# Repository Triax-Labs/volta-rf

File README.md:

> [!CAUTION]
> We claim **ZERO responsibility** against individuals who choose to operate, produce or sell this hardware. This repository exists strictly for educational & research purposes only.
>
> All tests for this hardware were done inside a controlled lab environment with all the proper local licenses needed for needed experiments.
>
> Please mind your local radio & telecommunication laws.

# VoltaRF

VoltaRF is a homebrew software defined radio (SDR), it is based on parts found inside a cheap 'n old satellite DVB-S television receiver.

VoltaRF could also be used as an expressive development board around the CH32H417 flagship platform, all GPIOs are exposed!

## Background

Due to the fact that RTL-SDRs are quite hard to find locally (due to restrictions), I have decided to build my own alternative out of already existing and easily available appliances.

The RTL-SDR itself being a by product of a television related product, I decided to base my own SDR on satellite television receiver parts, most notably the RF tuner found inside those.

After some testing I was able of finding out one very common RF tuner chip, the RDA5815. When it was put to testing I was able of getting it to tune in the range of 50MHz and all the way up to 2.5GHz (covering amateur bands, ISM, commercial broadcasting as well as radio-navigation and air traffic.)

The RDA5815 tuner claims a bandwidth range of 4MHz all the way up to 40MHz, thankfully the LPF is configurable over I2C. I can only guarantee 4MHz of bandwidth, unless the ADCs were overclocked.

## Main Parts

- SkyWorks' RDA5815M (RF Interface & Tuner)
- Qorvo's (ironically, part of SkyWorks now) SGL0622Z (LNA)
- WCH's CH32H417QEU6 (MCU, ADC and USB Interface)

[Here you find the entirety of the BOM.](https://github.com/Triax-Labs/volta-rf/blob/main/hardware/production/bom.csv)

## Production

Production is done through [JLCPCB](https://jlcpcb.com)'s PCBA service.

| Item | Price | Qty      |
| ---- | ----- | -------- |
| PCB  | $8    | 5 Boards |
| PCBA | $120  | 5 Boards |

_Those are estimated prices, and they don't include shipping._

Production files could be found inside `/hardware/production`, the BOM has been optimized for JLC's library of parts.

When ordering an assembled board, make sure all footprints are rotated in their right place with dots aligning.

Some parts don't exist on JLCPCB, so you will have to source and assemble them yourself, most notable one is the RDA5815M RF tuner chip, you can buy it from AliExpress instead.

---

---

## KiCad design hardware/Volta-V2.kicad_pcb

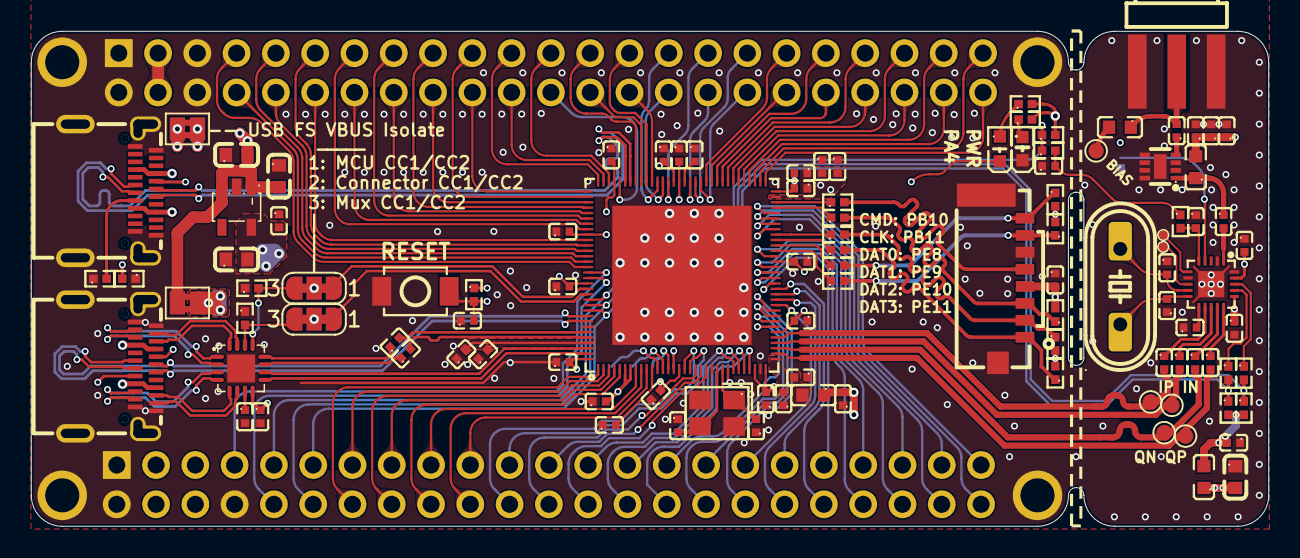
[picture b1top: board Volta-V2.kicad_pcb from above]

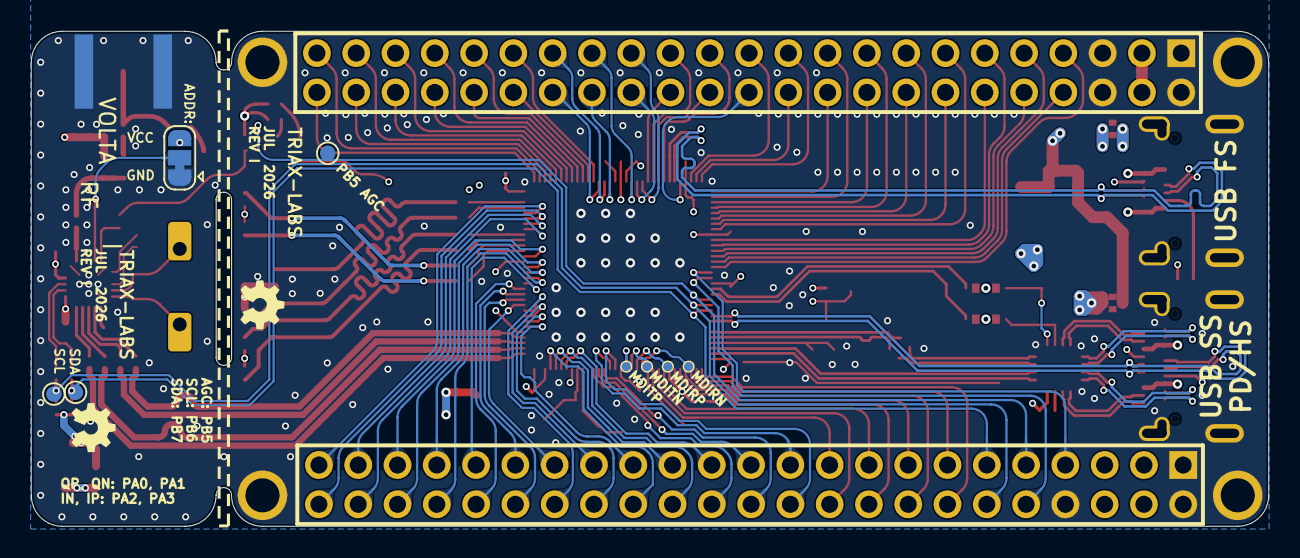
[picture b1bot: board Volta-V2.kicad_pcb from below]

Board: 4 copper layers, 80.0 x 32.0 mm, 116 parts (10 on the bottom side), 161 nets.

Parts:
C1, C2, C5, C6, C9, C10, C11, C15, C16, C17, C18, C19, C20, C21, C22, C23, C24, C25, C26, C27, C28, C29, C30, C31, C32, C33, C34, C35, C36, C37, C38, C39, C40, C45, C46, C50, C52: CL05B104KO5NNNC; C0402
C3, C4, C51: CL05A225MQ5NSNC; C0402
C7, C8: CL05B104KB54PNC; C0402
C12, C13, C14: CL10A475KO8NNNC; C0603
C41, C42: 0402B102K500NT; C0402
C43, C44: 0402CG150J500NT; C0402
C47, C48: 0402CG270J500NTN; C0402
C49: CL10A225KO8NNNC; C0603
Card1: TF-021B-H265; TF-SMD_TF-021B-H265
JP1: CC1; SolderJumper-3_P1.3mm_Bridged123_RoundedPad1.0x1.5mm_Number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
JP2: CC2; SolderJumper-3_P1.3mm_Bridged123_RoundedPad1.0x1.5mm_Number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
JP3, JP5: VBUS_IS_5V; SolderJumper-2_P1.3mm_Bridged2Bar_Pad1.0x1.5mm
JP4: SolderJumper_3_Bridged12; SolderJumper-3_P1.3mm_Bridged12_RoundedPad1.0x1.5mm
L1, L4: BLM18PG121SN1D_C14709; L0603
L2, L3: SDCL1608C68NJTF; L0603
LED1: KT-0603R; LED-SMD_L1.6-W0.8-R-RD
LED2: 0603White light_C2290; LED0603-R-RD_WHITE
R1, R2, R3, R4, R5, R8: 0402WGF220JTCE; R0402
R6, R7, R9, R10, R19, R20, R21: 0402WGF5601TCE; R0402
R11, R12, R13, R14, R15: 0402WGF1502TCE; R0402
R16, R17: 0402WGF3300TCE; R0402
R22, R23: 0402WGF499JTCE; R0402
R24, R25, R26: 0402WGF2001TCE; R0402
RF1: BWSMA-KE-P001; SMA-SMD_BWSMA-KE-P001
SW2: TS-1088-AR02016; SW-SMD_L3.9-W3.0-P4.45
TP1: MDIRN; 2xTinyTestPoint
TP2: MDIRP; 2xTinyTestPoint
TP3: MDITN; 2xTinyTestPoint
TP4: MDITP; 2xTinyTestPoint
TP5: IN; TestPoint_Pad_D1.0mm
TP6: QP; TestPoint_Pad_D1.0mm
TP7: QN; TestPoint_Pad_D1.0mm
TP8: IP; TestPoint_Pad_D1.0mm
TP9: AGC; TestPoint_Pad_D1.0mm
TP10: SDA; TestPoint_Pad_D1.0mm
TP11: SCL; TestPoint_Pad_D1.0mm
TP12: XOUT_EN; 2xTinyTestPoint
TP13: XOUT; 2xTinyTestPoint
TP14: BIAS-T; TestPoint_Pad_D1.0mm
U1, U8: DS1021-2X23SF11-B; HDR-TH_46P-P2.54-V-M-R2-C23-S2.54
U2: CH32H417QEU6_C49363240; QFN-128_L12.3-W12.3-P0.35-TL-EP9.0
U3: CH9441P; VQFN-16_L3.0-W3.0-P0.50-BL-EP1.8
U4: ME6217C33M5G; SOT-23-5_L3.0-W1.7-P0.95-LS2.8-BR
U6: RDA5815M; QFN-20_L3.0-W3.0-P0.40-TL-EP1.7
U7: SGL0622Z; DFN-8_L2.0-W2.0-P0.50-TL-EP
USB1, USB2: HC-TYPE-C-24P-035A; USB-C-SMD_TYPEC-324G-BCP24
X1: X322525MOB4SI; CRYSTAL-SMD_4P-L3.2-W2.5-BL
X2: X49SD27MSD2SC; HC-49US_L11.5-W4.5-P4.88

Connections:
+3.3V: C4.2, C14.2, C15.2, C16.2, C17.2, C20.2, C21.2, C22.2, C23.2, C24.2, C25.2, C26.2, C27.2, C28.2, C29.2, C49.2, Card1.4 (VDD), L1.1, L4.1, R11.2, R12.2, R13.2, R14.2, R15.2, R16.2, R17.2, R19.1, R24.2, U1.3, U1.4, U1.5, U1.6, U2.6 (VDDIO), U2.7 (VBAT), U2.16 (VDD33), U2.30 (VDDIO), U2.32 (VREFP), U2.38 (VDDIO), U2.51 (VDDIO), U2.64 (VDDIO), U2.82 (VDDIO), U2.93 (VDD33), U2.114 (VDDIO), U2.128 (VDD33), U4.5 (VOUT)
GND: C1.1, C2.1, C3.1, C4.1, C7.2, C8.2, C9.1, C10.1, C11.1, C12.1, C13.1, C14.1, C15.1, C16.1, C17.1, C18.1, C19.1, C20.1, C21.1, C22.1, C23.1, C24.1, C25.1, C26.1, C27.1, C28.1, C29.1, C30.2, C31.1, C32.1, C33.1, C38.2, C39.2, C40.2, C41.1, C42.1, C43.1, C44.1, C47.1, C48.1, C49.1, C50.1, C51.1, C52.1, Card1.6 (VSS), Card1.9, Card1.10, JP4.1 (A), LED1.2 (K), R6.1, R7.1, R9.1, R10.1, RF1.1, RF1.2, RF1.3, RF1.4, SW2.2, U1.1, U1.2, U1.8, U2.22 (VSS), U2.31 (VSSA), U2.122 (VSS), U2.129 (VSS), U3.17 (EP), U4.2 (VSS), U6.2 (GND), U6.7 (GND), U6.20 (GND), U6.21 (GND), U7.2 (GND), U7.3 (NC), U7.5 (NC), U7.6 (NC), U7.7 (NC), U7.8 (NC), U7.9 (PAD), U8.1, U8.2, U8.5, U8.6, USB1.1 (EP), USB1.2 (EP), USB1.3 (EP), USB1.4 (EP), USB1.A1 (GND), USB1.A12 (GND), USB1.B1 (GND), USB1.B12 (GND), USB2.1 (EP), USB2.2 (EP), USB2.3 (EP), USB2.4 (EP), USB2.A1 (GND), USB2.A12 (GND), USB2.B1 (GND), USB2.B12 (GND), X1.2 (GND), X1.4 (GND)
GPIO_PA4: LED2.2 (K), U1.29, U2.39 (PA4/ADC4/OP3_O1/DAC1)
GPIO_PA5: U1.32, U2.40 (PA5/ADC5/OP1_O1/DAC2)
GPIO_PA6: U1.31, U2.41 (PA6/ADC6/OP1_P1)
GPIO_PA7: U1.34, U2.42 (PA7/ADC7/OP1_N1)
GPIO_PA8: U2.87 (PA8), U8.27
GPIO_PA9: U2.88 (PA9/OTG_VBUS), U8.26
GPIO_PA10: U2.89 (PA10/OTG_ID), U8.25
GPIO_PA13: U2.92 (PA13), U8.24
GPIO_PA14: U2.94 (PA14), U8.23
GPIO_PA15: U2.95 (PA15), U8.22
GPIO_PB0: U1.35, U2.45 (PB0/ADC8/OP1_P0/CMP_P0)
GPIO_PB1: U1.38, U2.46 (PB1/ADC9/OP1_N0/OP2_O1/CMP_N0)
GPIO_PB2: U1.37, U2.47 (PB2/CMP_P1)
GPIO_PB5: R24.1, R26.1, TP9.1 (1_1), U1.9, U2.117 (PB5)
GPIO_PB6: R21.1, R23.2, TP11.1 (1_1), U1.12, U2.118 (PB6)
GPIO_PB7: R20.1, R22.2, TP10.1 (1_1), U1.11, U2.119 (PB7)
GPIO_PB12: U2.65 (PB12), U8.46
GPIO_PB13: U2.66 (PB13), U8.45
GPIO_PB14: U2.67 (PB14), U8.44
GPIO_PB15: U2.68 (PB15), U8.43
GPIO_PC0: U1.25, U2.26 (PC0/ADC10/HSADC0)
GPIO_PC1: U1.28, U2.27 (PC1/ADC11/HSADC1)
GPIO_PC2: U1.27, U2.28 (PC2/ADC12/HSADC2/OP3_P0)
GPIO_PC3: U1.30, U2.29 (PC3/ADC13/HSADC3/OP3_N0)
GPIO_PC4: U1.33, U2.43 (PC4/ADC14/OP1_O0/CMP_N1)
GPIO_PC5: U1.36, U2.44 (PC5/ADC15)
GPIO_PC6: U2.83 (PC6), U8.31
GPIO_PC7: U2.84 (PC7), U8.30
GPIO_PC8: U2.85 (PC8), U8.29
GPIO_PC9: U2.86 (PC9), U8.28
GPIO_PC10: U2.96 (PC10), U8.21
GPIO_PC11: U2.97 (PC11), U8.20
GPIO_PC12: U2.98 (PC12), U8.19
GPIO_PC13: U1.17, U2.8 (PC13)
GPIO_PC14: U1.20, U2.9 (PC14)
GPIO_PC15: U1.19, U2.10 (PC15)
GPIO_PD0: U2.99 (PD0), U8.18
GPIO_PD1: U2.100 (PD1), U8.17
GPIO_PD2: U2.101 (PD2), U8.16
GPIO_PD3: U2.102 (PD3), U8.15
GPIO_PD4: U2.103 (PD4), U8.14
GPIO_PD5: U2.104 (PD5), U8.13
GPIO_PD6: U2.106 (PD6), U8.12
GPIO_PD7: U2.107 (PD7), U8.11
GPIO_PD8: U2.69 (PD8), U8.42
GPIO_PD9: U2.70 (PD9), U8.41
GPIO_PD10: U2.71 (PD10), U8.40
GPIO_PD11: U2.72 (PD11), U8.39
GPIO_PD12: U2.73 (PD12), U8.38
GPIO_PD13: U2.74 (PD13), U8.37
GPIO_PD14: U2.75 (PD14), U8.36
GPIO_PD15: U2.76 (PD15), U8.35
GPIO_PE0: U2.111 (PE0), U8.7
GPIO_PE1: U1.7, U2.112 (PE1)
GPIO_PE2: U1.14, U2.1 (PE2)
GPIO_PE3: U1.13, U2.2 (PE3/SERDES_TXP)
GPIO_PE4: U1.16, U2.3 (PE4/SERDES_TXN)
GPIO_PE5: U1.15, U2.4 (PE5/SERDES_RXP)
GPIO_PE6: U1.18, U2.5 (PE6/SERDES_RXN)
GPIO_PE7: U1.41, U2.52 (PE7/OP2_O0)
GPIO_PE12: U1.44, U2.57 (PE12)
GPIO_PE13: U1.43, U2.58 (PE13)
GPIO_PE14: U1.46, U2.59 (PE14)
GPIO_PE15: U1.45, U2.60 (PE15)
GPIO_PF0: U2.77 (PF0), U8.34
GPIO_PF1: U2.78 (PF1), U8.33
GPIO_PF2: U2.79 (PF2), U8.32
GPIO_PF3: U2.108 (PF3), U8.10
GPIO_PF4: U2.109 (PF4), U8.9
GPIO_PF5: U2.110 (PF5), U8.8
GPIO_PF6: U1.22, U2.17 (PF6)
GPIO_PF7: U1.21, U2.18 (PF7)
GPIO_PF8: U1.24, U2.19 (PF8/HSADC4)
GPIO_PF9: U1.23, U2.20 (PF9/HSADC5)
GPIO_PF10: U1.26, U2.21 (PF10/HSADC6)
GPIO_PF11: U1.40, U2.48 (PF11/OP2_P1)
GPIO_PF12: U1.39, U2.49 (PF12/OP2_N1)
GPIO_PF13: U1.42, U2.50 (PF13)
GPIO_PF14: U1.10, U2.113 (PF14)
unnamed: C1.2, U2.11 (VDDK)
unnamed: C2.2, U2.80 (VDDK)
unnamed: C42.2, R25.1, R26.2
unnamed: C46.2, L2.1, RF1.5
unnamed: JP1.3 (B), R7.2, U3.13 (CC1)
unnamed: JP2.3 (B), R6.2, U3.14 (CC2)
unnamed: JP4.2 (C), U6.4 (ADDR)
unnamed: JP5.1 (A), USB2.A4 (VBUS), USB2.A9 (VBUS), USB2.B4 (VBUS), USB2.B9 (VBUS)
unnamed: L2.2, TP14.1 (1_1)
unnamed: LED1.1 (A), R16.1
unnamed: LED2.1 (A), R17.1
unnamed: TP1.1 (1_1), U2.12 (MDIRN)
unnamed: TP2.1 (1_1), U2.13 (MDIRP)
unnamed: TP3.1 (1_1), U2.14 (MDITN)
unnamed: TP4.1 (1_1), U2.15 (MDITP)
unnamed: R5.1, U2.61 (PB10)
unnamed: R8.1, U2.62 (PB11)
unnamed: R1.1, U2.53 (PE8/OP2_N0)
unnamed: R2.1, U2.54 (PE9/OP2_P0)
unnamed: R3.1, U2.55 (PE10)
unnamed: R4.1, U2.56 (PE11)
unnamed: C51.2, C52.2, U2.125 (VDD12A)
unnamed: C5.1, U3.12 (SSTX)
unnamed: C6.1, U3.11 (SSTY)
unnamed: C8.1, U3.7 (VDD)
unnamed: C41.2, R25.2, U6.5 (AGC)
unnamed: C35.1, U6.13 (BBIN)
unnamed: C34.1, U6.12 (BBIP)
unnamed: C36.1, U6.14 (BBQN)
unnamed: C37.1, U6.15 (BBQP)
unnamed: C32.2, U6.11 (DVDD)
unnamed: R23.1, U6.18 (SCL)
unnamed: R22.1, U6.17 (SDA)
unnamed: TP13.1 (1_1), U6.8 (XOUT)
unnamed: TP12.1 (1_1), U6.6 (XOUT_EN)
unnamed: C46.1, U7.4 (RF_IN)
unnamed: C45.1, L3.1, U7.1 (RF_OUT)
RESET_BTN: C33.2, R19.2, SW2.1, U2.25 (NRST)
RF_FEED: C45.2, U6.1 (RFIP)
RF_IN: C35.2, TP5.1 (1_1), U2.36 (PA2/ADC2/OP3_P1)
RF_IP: C34.2, TP8.1 (1_1), U2.37 (PA3/ADC3/OP3_N1)
RF_QN: C36.2, TP7.1 (1_1), U2.35 (PA1/ADC1)
RF_QP: C37.2, TP6.1 (1_1), U2.34 (PA0/ADC0/OP3_O0)
RF_VCC: C30.1, C31.2, C38.1, C39.1, C40.1, C50.2, JP4.3 (B), L3.2, L4.2, R20.2, R21.2, U6.16 (VCC), U6.19 (VCC)
RF_XTAL_IN: C47.2, U6.9 (XTAL_IN), X2.2 (OSC2)
RF_XTAL_OUT: C48.2, U6.10 (XTAL_OUT), X2.1 (OSC1)
SD_CLK: Card1.5 (CLX), R8.2
SD_CMD: Card1.3 (CMD), R5.2, R15.1
SD_DAT0: Card1.7 (DAT0), R1.2, R14.1
SD_DAT1: Card1.8 (DAT1), R2.2, R12.1
SD_DAT2: Card1.1 (DAT2), R3.2, R11.1
SD_DAT3: Card1.2 (CD/DAT3), R4.2, R13.1
SYS_XTAL_IN: C44.2, U2.23 (XI), X1.3 (OSC2)
SYS_XTAL_OUT: C43.2, U2.24 (XO), X1.1 (OSC1)
USBFS_CC1: R9.2, USB2.A5 (CC1)
USBFS_CC2: R10.2, USB2.B5 (CC2)
USBFS_DN: U2.90 (PA11/OTG_DM), USB2.A7 (DN1), USB2.B7 (DN2)
USBFS_DP: U2.91 (PA12/OTG_DP), USB2.A6 (DP1), USB2.B6 (DP2)
USBSS_CC1: JP1.2 (C), USB1.A5 (CC1)
USBSS_CC2: JP2.2 (C), USB1.B5 (CC2)
USBSS_DN: U2.121 (PB9/USB2DM/SWDIO), USB1.A7 (DN1), USB1.B7 (DN2)
USBSS_DP: U2.120 (PB8/USB2DP/SWCLK), USB1.A6 (DP1), USB1.B6 (DP2)
USBSS_OPT_CC1: JP1.1 (A), U2.115 (PB3/CC1)
USBSS_OPT_CC2: JP2.1 (A), U2.116 (PB4/CC2)
USBSS_RX1N: U3.2 (SSR1Y), USB1.B10 (SSRXn1)
USBSS_RX1P: U3.1 (SSR1X), USB1.B11 (SSRXp1)
USBSS_RX2N: U3.5 (SSR2X), USB1.A10 (SSRXn2)
USBSS_RX2P: U3.6 (SSR2Y), USB1.A11 (SSRXp2)
USBSS_RXN: U2.126 (SSRXB), U3.10 (SSRX)
USBSS_RXP: U2.127 (SSRXA), U3.9 (SSRY)
USBSS_TX1N: U3.16 (SST1Y), USB1.A3 (SSTXn1)
USBSS_TX1P: U3.15 (SST1X), USB1.A2 (SSTXP1)
USBSS_TX2N: U3.3 (SST2X), USB1.B3 (SSTXn2)
USBSS_TX2P: U3.4 (SST2Y), USB1.B2 (SSTXp2)
USBSS_TXN: C5.2, U2.123 (SSTXB)
USBSS_TXP: C6.2, U2.124 (SSTXA)
VBUS: C7.1, JP3.2 (B), JP5.2 (B), U3.8 (VBUS), USB1.A4 (VBUS), USB1.A9 (VBUS), USB1.B4 (VBUS), USB1.B9 (VBUS)
VBUS_SAFE: C12.2, C13.2, JP3.1 (A), U4.1 (VIN), U4.3 (CE), U8.3, U8.4
VDDA: C18.2, C19.2, L1.2, U2.33 (VDD33A)
VDD_1.8V: C3.2, C9.2, C10.2, C11.2, U2.63 (VIO18), U2.81 (VIO18), U2.105 (VIO18)

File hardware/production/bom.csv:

Designator,Footprint,Quantity,Value,LCSC Part #
"_4, _3, _2, ",,4,,
"C1, C10, C11, C15, C16, C17, C18, C19, C2, C20, C21, C22, C23, C24, C25, C26, C27, C28, C29, C30, C31, C32, C33, C34, C35, C36, C37, C38, C39, C40, C45, C46, C5, C50, C52, C6, C9",C0402,37,CL05B104KO5NNNC,C1525
"C12, C13, C14",C0603,3,CL10A475KO8NNNC,C19666
"C3, C4, C51",C0402,3,CL05A225MQ5NSNC,C12530
"C41, C42",C0402,2,0402B102K500NT,C1523
"C43, C44",C0402,2,0402CG150J500NT,C1548
"C47, C48",C0402,2,0402CG270J500NTN,C1557
C49,C0603,1,CL10A225KO8NNNC,C23630
"C7, C8",C0402,2,CL05B104KB54PNC,C307331
CARD1,TF-SMD_TF-021B-H265,1,TF-021B-H265,C498185
"L1, L4",L0603,2,BLM18PG121SN1D_C14709,C14709
"L2, L3",L0603,2,SDCL1608C68NJTF,C13415
LED1,LED-SMD_L1.6-W0.8-R-RD,1,KT-0603R,C2286
LED2,LED0603-R-RD_WHITE,1,0603White light_C2290,C2290
"R1, R2, R3, R4, R5, R8",R0402,6,0402WGF220JTCE,C25092
"R10, R19, R20, R21, R6, R7, R9",R0402,7,0402WGF5601TCE,C25908
"R11, R12, R13, R14, R15",R0402,5,0402WGF1502TCE,C25756
"R16, R17",R0402,2,0402WGF3300TCE,C25104
"R22, R23",R0402,2,0402WGF499JTCE,C25120
"R24, R25, R26",R0402,3,0402WGF2001TCE,C4109
SW2,SW-SMD_L3.9-W3.0-P4.45,1,TS-1088-AR02016,C720477
"U1, U8",HDR-TH_46P-P2.54-V-M-R2-C23-S2.54,2,DS1021-2X23SF11-B,C7430419
U2,QFN-128_L12.3-W12.3-P0.35-TL-EP9.0,1,CH32H417QEU6_C49363240,C49363240
U3,VQFN-16_L3.0-W3.0-P0.50-BL-EP1.8,1,CH9441P,C54300797
U4,SOT-23-5_L3.0-W1.7-P0.95-LS2.8-BR,1,ME6217C33M5G,C427602
U7,DFN-8_L2.0-W2.0-P0.50-TL-EP,1,SGL0622Z,C470895
"USB1, USB2",USB-C-SMD_TYPEC-324G-BCP24,2,HC-TYPE-C-24P-035A,C48887178
X1,CRYSTAL-SMD_4P-L3.2-W2.5-BL,1,X322525MOB4SI,C9006

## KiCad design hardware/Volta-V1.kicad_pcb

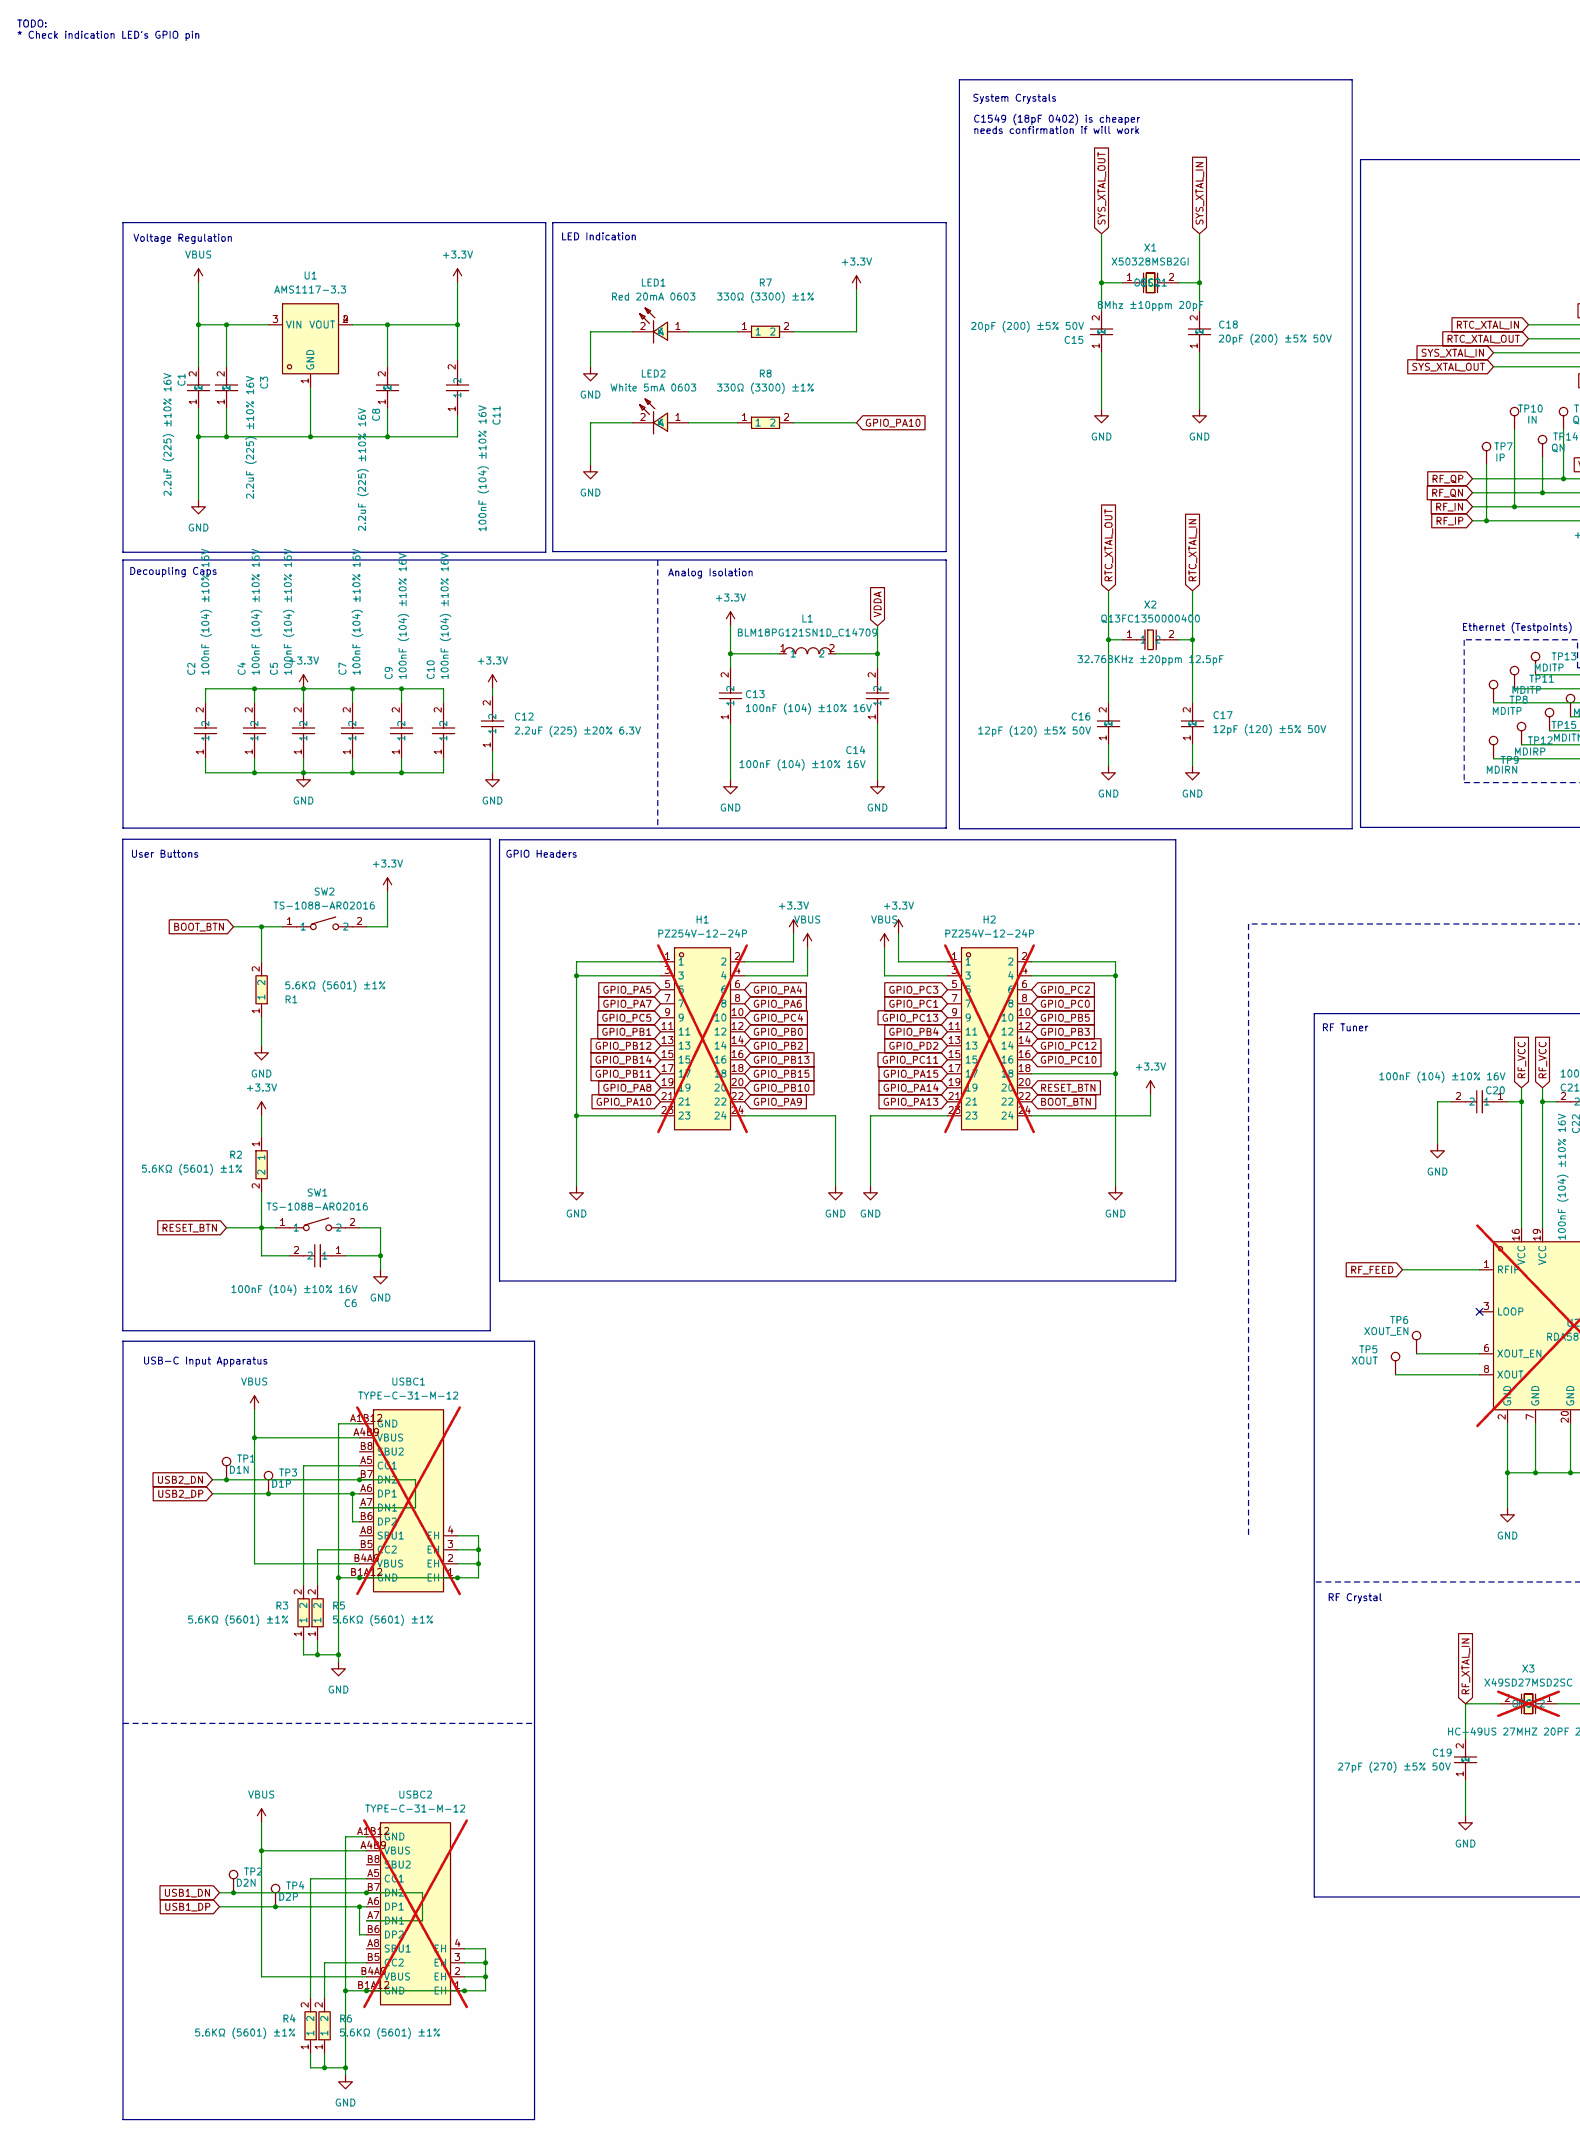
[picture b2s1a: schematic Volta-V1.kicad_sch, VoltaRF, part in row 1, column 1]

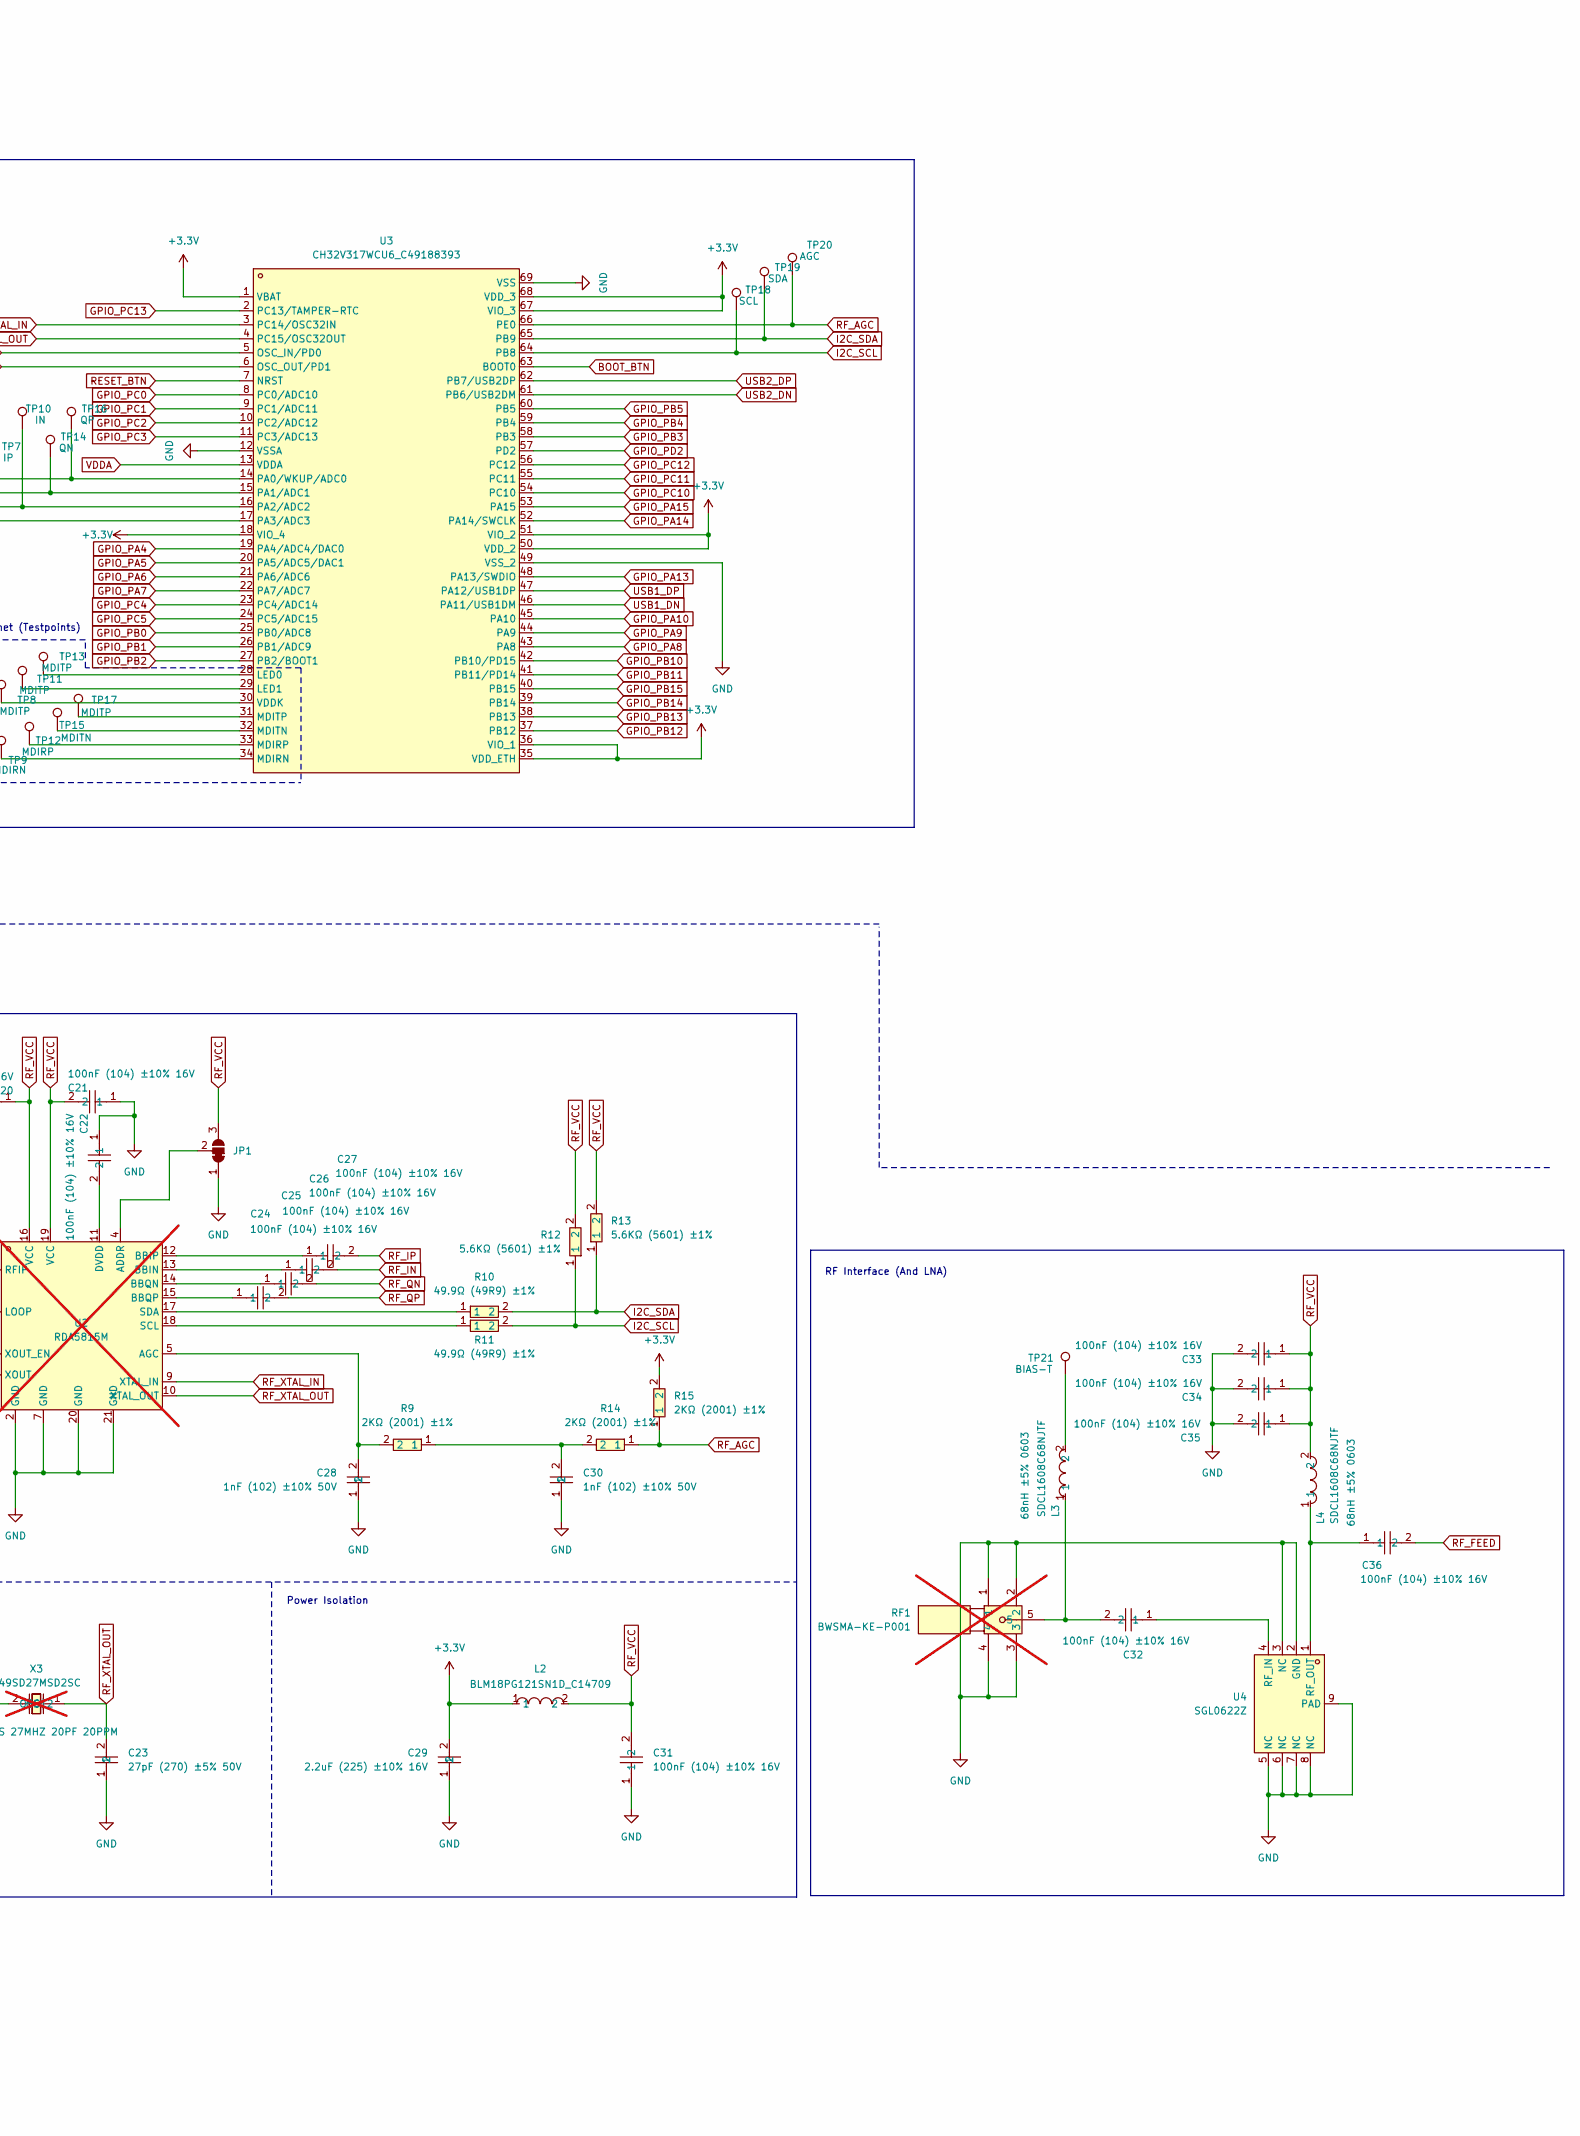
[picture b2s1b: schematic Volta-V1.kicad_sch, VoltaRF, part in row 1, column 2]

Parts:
C1, C3, C8, C29: CL10A225KO8NNNC; C0603; MPN CL10A225KO8NNNC; LCSC Part C23630
C2, C4, C5, C6, C7, C9, C10, C11, C13, C14, C20, C21, C22, C24, C25, C26, C27, C31, C32, C33, C34, C35, C36: CL05B104KO5NNNC; C0402; MPN CL05B104KO5NNNC; LCSC Part C1525
C12: CL05A225MQ5NSNC; C0402; MPN CL05A225MQ5NSNC; LCSC Part C12530
C15, C18: 0402CG200J500NT; C0402; MPN 0402CG200J500NT; LCSC Part C1554
C16, C17: 0402CG120J500NT; C0402; MPN 0402CG120J500NT; LCSC Part C1547
C19, C23: 0402CG270J500NTN; C0402; MPN 0402CG270J500NT; LCSC Part C1557
C28, C30: 0402B102K500NT; C0402; MPN 0402B102K500NT; LCSC Part C1523
H1, H2: PZ254V-12-24P; HDR-TH_24P-P2.54-V-M-R2-C12-S2.54; MPN PZ254V-12-24P; LCSC Part C492429; not fitted
JP1: SolderJumper_3_Bridged12; SolderJumper-3_P1.3mm_Bridged12_RoundedPad1.0x1.5mm
L1, L2: BLM18PG121SN1D_C14709; L0603; MPN BLM18PG121SN1D; LCSC Part C14709
L3, L4: SDCL1608C68NJTF; L0603; MPN SDCL1608C68NJTDF; LCSC Part C13415
LED1: KT-0603R; LED-SMD_L1.6-W0.8-R-RD; MPN KT-0603R; LCSC Part C2286
LED2: 0603White light_C2290; LED0603-R-RD_WHITE; MPN KT-0603W; LCSC Part C2290
R1, R2, R3, R4, R5, R6, R12, R13: 0402WGF5601TCE; R0402; MPN 0402WGF5601TCE; LCSC Part C25908
R7, R8: 0402WGF3300TCE; R0402; MPN 0402WGF3300TCE; LCSC Part C25104
R9, R14, R15: 0402WGF2001TCE; R0402; MPN 0402WGF2001TCE; LCSC Part C4109
R10, R11: 0402WGF499JTCE; R0402; MPN 0402WGF499JTCE; LCSC Part C25120
RF1: BWSMA-KE-P001; SMA-SMD_BWSMA-KE-P001; MPN BWSMA-KE-P001; LCSC Part C496550; not fitted
SW1, SW2: TS-1088-AR02016; SW-SMD_L3.9-W3.0-P4.45; LCSC Part C720477
TP1: D1N; TestPoint_Pad_D1.0mm
TP2: D2N; TestPoint_Pad_D1.0mm
TP3: D1P; TestPoint_Pad_D1.0mm
TP4: D2P; TestPoint_Pad_D1.0mm
TP5: XOUT; 2xTinyTestPoint
TP6: XOUT_EN; 2xTinyTestPoint
TP7: IP; TestPoint_Pad_D1.0mm
TP8, TP11, TP13, TP17: MDITP; 2xTinyTestPoint
TP9: MDIRN; 2xTinyTestPoint
TP10: IN; TestPoint_Pad_D1.0mm
TP12: MDIRP; 2xTinyTestPoint
TP14: QN; TestPoint_Pad_D1.0mm
TP15: MDITN; 2xTinyTestPoint
TP16: QP; TestPoint_Pad_D1.0mm
TP18: SCL; TestPoint_Pad_D1.0mm
TP19: SDA; TestPoint_Pad_D1.0mm
TP20: AGC; TestPoint_Pad_D1.0mm
TP21: BIAS-T; TestPoint_Pad_D1.0mm
U1: AMS1117-3.3; SOT-223-3_L6.5-W3.4-P2.30-LS7.0-BR; LCSC Part C6186
U2: RDA5815M; QFN-20_L3.0-W3.0-P0.40-TL-EP1.7; MPN Tuner,RDA5815M; LCSC Part C9900005759; not fitted
U3: CH32V317WCU6_C49188393; QFN-68_L8.0-W8.0-P0.40-TL-EP6.2; MPN CH32V317WCU6; LCSC Part C49188393
U4: SGL0622Z; DFN-8_L2.0-W2.0-P0.50-TL-EP; MPN SGL0622Z; LCSC Part C470895
USBC1, USBC2: TYPE-C-31-M-12; USB-C_SMD-TYPE-C-31-M-12_1; LCSC Part C165948; not fitted
X1: X50328MSB2GI; CRYSTAL-SMD_L5.0-W3.2; MPN X50328MSB2GI; LCSC Part C115962
X2: Q13FC1350000400; FC-135R_L3.2-W1.5; MPN Q13FC13500004; LCSC Part C32346
X3: X49SD27MSD2SC; HC-49US_L11.5-W4.5-P4.88; MPN X49SD27MSD2SC; LCSC Part C2216; not fitted

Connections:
+3.3V: C2.2, C4.2, C5.2, C7.2, C8.2, C9.2, C10.2, C11.2, C12.2, C13.2, C29.2, H1.2, H2.1, H2.24, L1.1, L2.1, R2.1, R7.2, R15.2, SW2.2, U1.2 (VOUT), U1.4 (VOUT), U3.1 (VBAT), U3.18 (VIO_4), U3.35 (VDD_ETH), U3.36 (VIO_1), U3.50 (VDD_2), U3.51 (VIO_2), U3.67 (VIO_3), U3.68 (VDD_3)
BOOT_BTN: H2.22, R1.2, SW2.1, U3.63 (BOOT0)
GND: C1.1, C2.1, C3.1, C4.1, C5.1, C6.1, C7.1, C8.1, C9.1, C10.1, C11.1, C12.1, C13.1, C14.1, C15.1, C16.1, C17.1, C18.1, C19.1, C20.2, C21.1, C22.1, C23.1, C28.1, C29.1, C30.1, C31.1, C33.2, C34.2, C35.2, H1.1, H1.3, H1.23, H1.24, H2.2, H2.4, H2.18, H2.23, JP1.1 (A), LED1.2 (K), LED2.2 (K), R1.1, R3.1, R4.1, R5.1, R6.1, RF1.1, RF1.2, RF1.3, RF1.4, SW1.2, U1.1 (GND), U2.2 (GND), U2.7 (GND), U2.20 (GND), U2.21 (GND), U3.12 (VSSA), U3.49 (VSS_2), U3.69 (VSS), U4.2 (GND), U4.3 (NC), U4.5 (NC), U4.6 (NC), U4.7 (NC), U4.8 (NC), U4.9 (PAD), USBC1.1 (EH), USBC1.2 (EH), USBC1.3 (EH), USBC1.4 (EH), USBC1.A1B12 (GND), USBC1.B1A12 (GND), USBC2.1 (EH), USBC2.2 (EH), USBC2.3 (EH), USBC2.4 (EH), USBC2.A1B12 (GND), USBC2.B1A12 (GND)
GPIO_PA4: H1.6, U3.19 (PA4/ADC4/DAC0)
GPIO_PA5: H1.5, U3.20 (PA5/ADC5/DAC1)
GPIO_PA6: H1.8, U3.21 (PA6/ADC6)
GPIO_PA7: H1.7, U3.22 (PA7/ADC7)
GPIO_PA8: H1.19, U3.43 (PA8)
GPIO_PA9: H1.22, U3.44 (PA9)
GPIO_PA10: H1.21, R8.2, U3.45 (PA10)
GPIO_PA13: H2.21, U3.48 (PA13/SWDIO)
GPIO_PA14: H2.19, U3.52 (PA14/SWCLK)
GPIO_PA15: H2.17, U3.53 (PA15)
GPIO_PB0: H1.12, U3.25 (PB0/ADC8)
GPIO_PB1: H1.11, U3.26 (PB1/ADC9)
GPIO_PB2: H1.14, U3.27 (PB2/BOOT1)
GPIO_PB3: H2.12, U3.58 (PB3)
GPIO_PB4: H2.11, U3.59 (PB4)
GPIO_PB5: H2.10, U3.60 (PB5)
GPIO_PB10: H1.20, U3.42 (PB10/PD15)
GPIO_PB11: H1.17, U3.41 (PB11/PD14)
GPIO_PB12: H1.13, U3.37 (PB12)
GPIO_PB13: H1.16, U3.38 (PB13)
GPIO_PB14: H1.15, U3.39 (PB14)
GPIO_PB15: H1.18, U3.40 (PB15)
GPIO_PC0: H2.8, U3.8 (PC0/ADC10)
GPIO_PC1: H2.7, U3.9 (PC1/ADC11)
GPIO_PC2: H2.6, U3.10 (PC2/ADC12)
GPIO_PC3: H2.5, U3.11 (PC3/ADC13)
GPIO_PC4: H1.10, U3.23 (PC4/ADC14)
GPIO_PC5: H1.9, U3.24 (PC5/ADC15)
GPIO_PC10: H2.16, U3.54 (PC10)
GPIO_PC11: H2.15, U3.55 (PC11)
GPIO_PC12: H2.14, U3.56 (PC12)
GPIO_PC13: H2.9, U3.2 (PC13/TAMPER-RTC)
GPIO_PD2: H2.13, U3.57 (PD2)
I2C_SCL: R11.2, R12.1, TP18.1, U3.64 (PB8)
I2C_SDA: R10.2, R13.1, TP19.1, U3.65 (PB9)
unnamed: C30.2, R9.1, R14.2
unnamed: C32.2, L3.1, RF1.5
unnamed: JP1.2 (C), U2.4 (ADDR)
unnamed: L3.2, TP21.1
unnamed: LED1.1 (A), R7.1
unnamed: LED2.1 (A), R8.1
unnamed: C28.2, R9.2, U2.5 (AGC)
unnamed: C26.1, U2.13 (BBIN)
unnamed: C27.1, U2.12 (BBIP)
unnamed: C25.1, U2.14 (BBQN)
unnamed: C24.1, U2.15 (BBQP)
unnamed: C22.2, U2.11 (DVDD)
unnamed: R11.1, U2.18 (SCL)
unnamed: R10.1, U2.17 (SDA)
unnamed: TP5.1, U2.8 (XOUT)
unnamed: TP6.1, U2.6 (XOUT_EN)
unnamed: TP13.1, U3.28 (LED0)
unnamed: TP11.1, U3.29 (LED1)
unnamed: TP9.1, U3.34 (MDIRN)
unnamed: TP12.1, U3.33 (MDIRP)
unnamed: TP15.1, U3.32 (MDITN)
unnamed: TP17.1, U3.31 (MDITP)
unnamed: TP8.1, U3.30 (VDDK)
unnamed: C32.1, U4.4 (RF_IN)
unnamed: C36.1, L4.1, U4.1 (RF_OUT)
unnamed: R3.2, USBC1.A5 (CC1)
unnamed: R5.2, USBC1.B5 (CC2)
unnamed: R4.2, USBC2.A5 (CC1)
unnamed: R6.2, USBC2.B5 (CC2)
RESET_BTN: C6.2, H2.20, R2.2, SW1.1, U3.7 (NRST)
RF_AGC: R14.1, R15.1, TP20.1, U3.66 (PE0)
RF_FEED: C36.2, U2.1 (RFIP)
RF_IN: C26.2, TP10.1, U3.16 (PA2/ADC2)
RF_IP: C27.2, TP7.1, U3.17 (PA3/ADC3)
RF_QN: C25.2, TP14.1, U3.15 (PA1/ADC1)
RF_QP: C24.2, TP16.1, U3.14 (PA0/WKUP/ADC0)
RF_VCC: C20.1, C21.2, C31.2, C33.1, C34.1, C35.1, JP1.3 (B), L2.2, L4.2, R12.2, R13.2, U2.16 (VCC), U2.19 (VCC)
RF_XTAL_IN: C19.2, U2.9 (XTAL_IN), X3.2 (OSC2)
RF_XTAL_OUT: C23.2, U2.10 (XTAL_OUT), X3.1 (OSC1)
RTC_XTAL_IN: C17.2, U3.3 (PC14/OSC32IN), X2.2
RTC_XTAL_OUT: C16.2, U3.4 (PC15/OSC32OUT), X2.1
SYS_XTAL_IN: C18.2, U3.5 (OSC_IN/PD0), X1.2 (OSC2)
SYS_XTAL_OUT: C15.2, U3.6 (OSC_OUT/PD1), X1.1 (OSC1)
USB1_DN: TP2.1, U3.46 (PA11/USB1DM), USBC2.A7 (DN1), USBC2.B7 (DN2)
USB1_DP: TP4.1, U3.47 (PA12/USB1DP), USBC2.A6 (DP1), USBC2.B6 (DP2)
USB2_DN: TP1.1, U3.61 (PB6/USB2DM), USBC1.A7 (DN1), USBC1.B7 (DN2)
USB2_DP: TP3.1, U3.62 (PB7/USB2DP), USBC1.A6 (DP1), USBC1.B6 (DP2)
VBUS: C1.2, C3.2, H1.4, H2.3, U1.3 (VIN), USBC1.A4B9 (VBUS), USBC1.B4A9 (VBUS), USBC2.A4B9 (VBUS), USBC2.B4A9 (VBUS)
VDDA: C14.2, L1.2, U3.13 (VDDA)

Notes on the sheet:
RF Tuner
LED Indication
RF Interface (And LNA)
GPIO Headers
Analog Isolation
USB-C Input Apparatus
Voltage Regulation
User Buttons
TODO: * Check indication LED's GPIO pin
Power Isolation
C1549 (18pF 0402) is cheaper needs confirmation if will work
Decoupling Caps
RF Crystal
Ethernet (Testpoints)
System Crystals

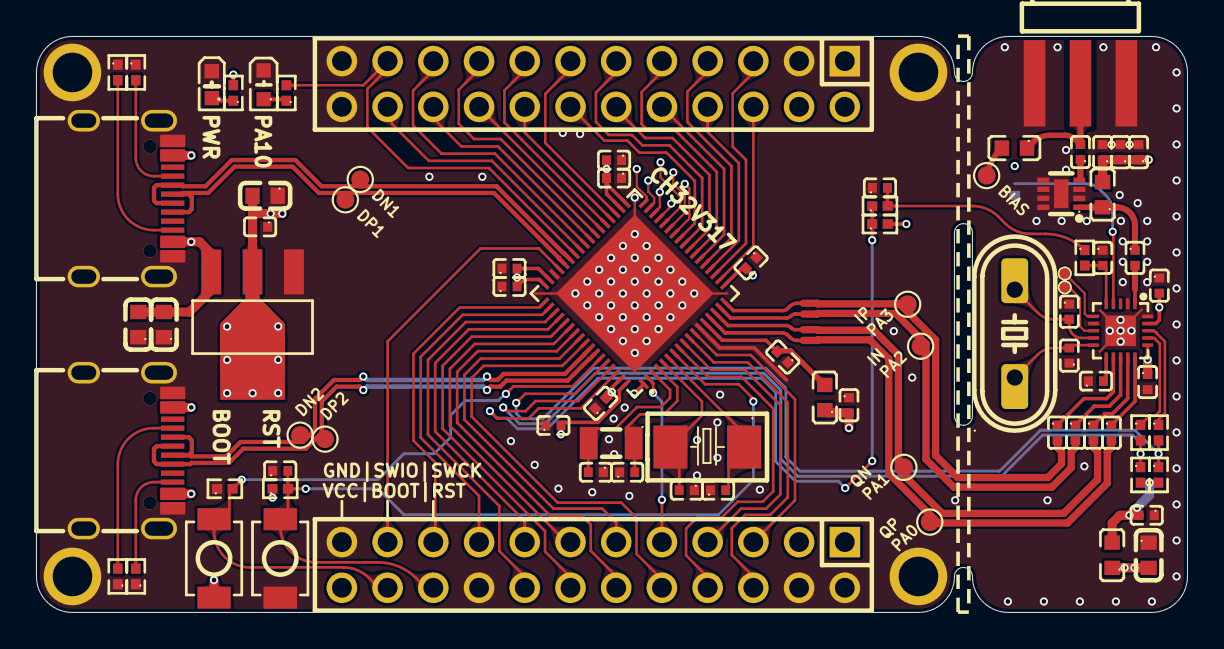
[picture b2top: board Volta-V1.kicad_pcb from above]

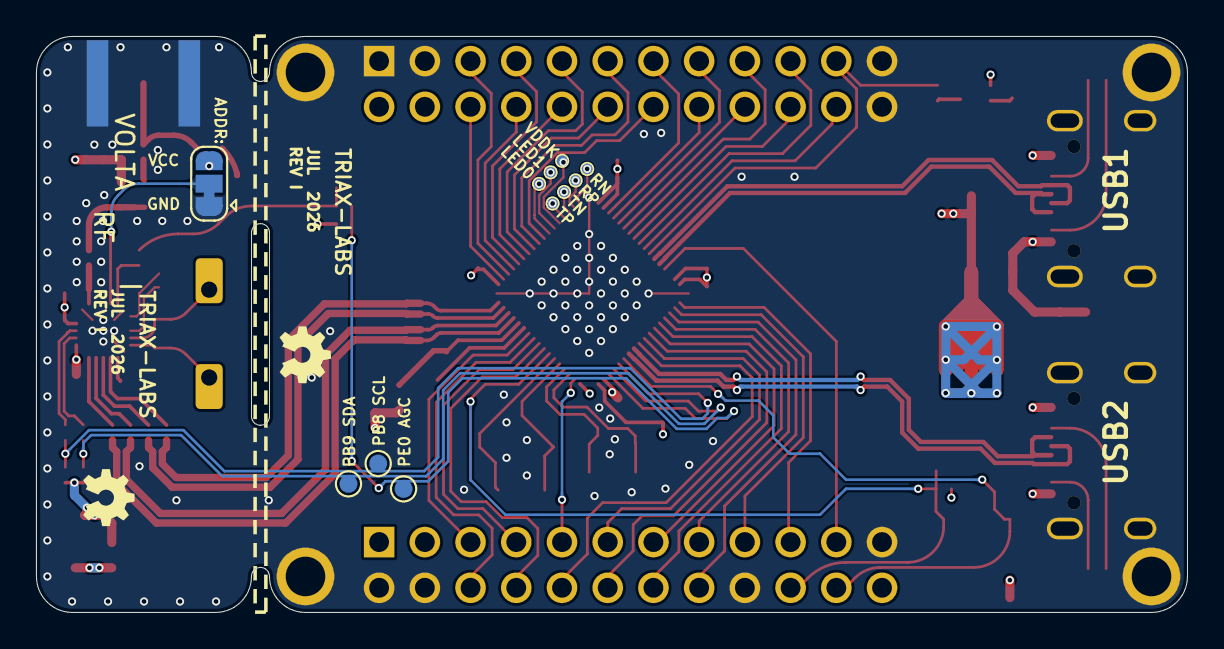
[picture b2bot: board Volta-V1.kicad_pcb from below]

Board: 4 copper layers, 63.9 x 32.0 mm, 93 parts (11 on the bottom side), 87 nets.

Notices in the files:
README.md:
CC BY-NC-ND 4.0
